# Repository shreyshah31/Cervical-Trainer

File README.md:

# Cervical-Trainer (Mend)

Cervical Trainer

Physiotherapists find difficult to have an accurate assessment tool and databse system to track the recovery cycle of the
pateint, the physiotherapists also needs to motivate the patient everyday to execise. 
Hence we have made a light, portable, handy device which has long lasting battery, which is connected to an android app via bluetooth. The app has a Training mode which helps in training sessions of patient, for tracing the recovery cycle there is an inbuilt database system , and for motivating and engrosing them to exercise daily we have built gaming mode ,where the patients play a game and exercise on daily basis.

Device : 

Hardware Used:
MPU6050,HC-05(Bluetooth),Arduino Nano,Lipo Battery,
Battery charging Module.

Software Used:
Android Studio,Arduio IDE

Working:
Here initially MPU6050 and Bluetooth is interfaced with
Arduino Nano.The communication protocol used for reading 
data value from MPU6050 is I2C and for Bluetooth USART 
is used.

1. Here first of all the data from MPU6050 is taken through
I2C protocol. These data are know to be raw data values.
After the data received by the controller Using mathematical 
algorithm we convert this raw data into yaw , roll and pitch.

2. Charging module is used to charge the Lipo Battery.here when the
battery is charged for 1hr it would run continuously 24hrs.

3. After getting this processed data,then this data is then transmitted 
to available Mobile phone (Here the bluetooth must be enabled before
the transmission of data) via UsART protocol.

4. Then we have made an Android application where the received data
is used by the Software application where we have used the this data
for the excerise of patients via analaysis and game mode, also graph
mode is also available to track the patient exercise.

5. Inside Android Application we decrypt the data by using y,p,r as the breaking points,
the data is processed and then used for the movements in game and the training modes.

6. Inside training mode there are 3 buttons X Y And Z , this button will help the patient to concentrate the
movement in that specific direction.

7. The record button will help the doctor to record the specific data into the database,
and hence will reduce the pen and paper useage of the doctor.

8. There are three games, each game is ment for specific direction movement only,
For each game there is a setting page.

9. The setting page will have 3 attributes 1) Range 2)Time 3)Difficulty.
This will help the doctor and patient to understand all the three attribuites and its effect on daily basis.

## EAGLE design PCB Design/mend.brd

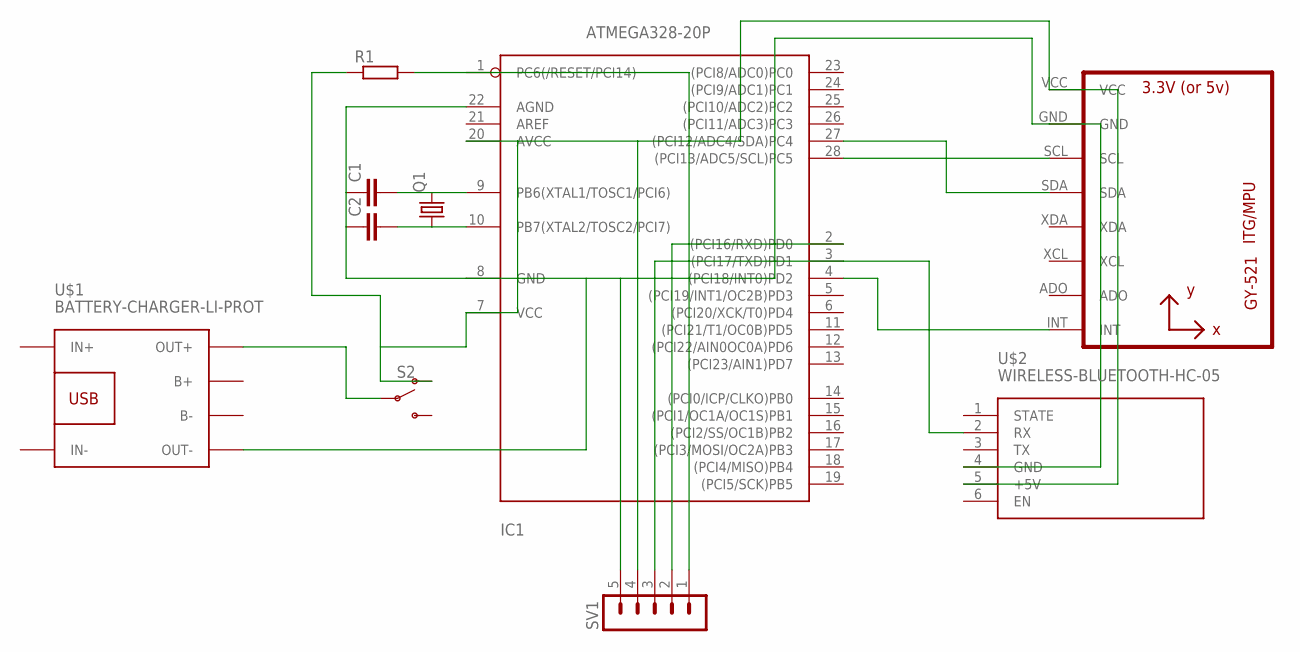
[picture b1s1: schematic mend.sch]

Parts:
C1, C2: C2.5/2; C2.5-2
IC1: ATMEGA328-20P; DIL28-3
Q1: CRYSTALHC49S; HC49/S
R1: R0204/7; 0204/7
S2: SWITCH-SPDT-PTH-8.6X4.3MM-LOCK; SWITCH_SPDT_8.6X4.3MM_LOCK
SV1: MA05-1
U1: GY-521MPU6050; GY-521
U$1: BATTERY-CHARGER-LI-PROT
U$2: WIRELESS-BLUETOOTH-HC-05

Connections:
unnamed: C1.2, IC1.9 (PB6(XTAL1/TOSC1/PCI6)), Q1.2
unnamed: C2.2, IC1.10 (PB7(XTAL2/TOSC2/PCI7)), Q1.1
unnamed: IC1.2 ((PCI16/RXD)PD0), SV1.2
unnamed: IC1.28 ((PCI13/ADC5/SCL)PC5), U1.SCL
unnamed: IC1.27 ((PCI12/ADC4/SDA)PC4), U1.SDA
unnamed: IC1.3 ((PCI17/TXD)PD1), SV1.3, U$2.2 (RX)
unnamed: IC1.4 ((PCI18/INT0)PD2), U1.INT
unnamed: S2.2, U$1.OUT+
unnamed: IC1.1 (PC6(/RESET/PCI14)), R1.2, SV1.1
unnamed: IC1.7 (VCC), IC1.20 (AVCC), R1.1, S2.1 (O), SV1.4, U1.VCC, U$2.5 (+5V)
unnamed: C1.1, C2.1, IC1.8 (GND), IC1.22 (AGND), SV1.5, U1.GND, U$1.OUT-, U$2.4 (GND)

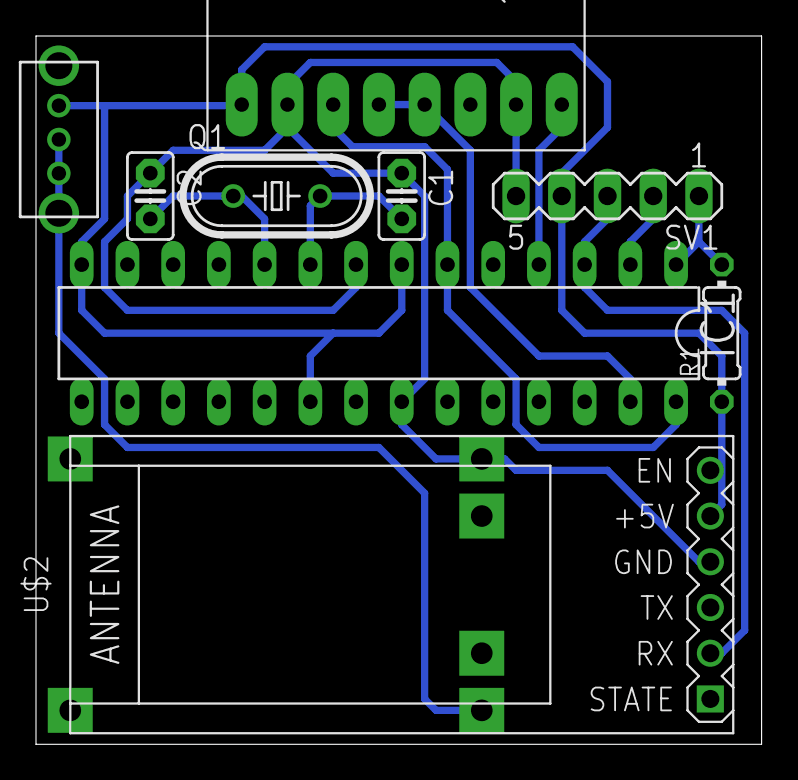
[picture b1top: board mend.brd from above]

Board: 2 copper layers, 40.3 x 39.3 mm, 10 parts (1 on the bottom side), 11 nets.

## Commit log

2020-01-31 Second Commit

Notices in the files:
parts and their libraries:
diy-modules: Released under the Creative Commons Attribution 4.0 International License: http://creativecommons.org/licenses/by/4.0
SparkFun-Switches: Licensing: Creative Commons ShareAlike 4.0 International - https://creativecommons.org/licenses/by-sa/4.0
